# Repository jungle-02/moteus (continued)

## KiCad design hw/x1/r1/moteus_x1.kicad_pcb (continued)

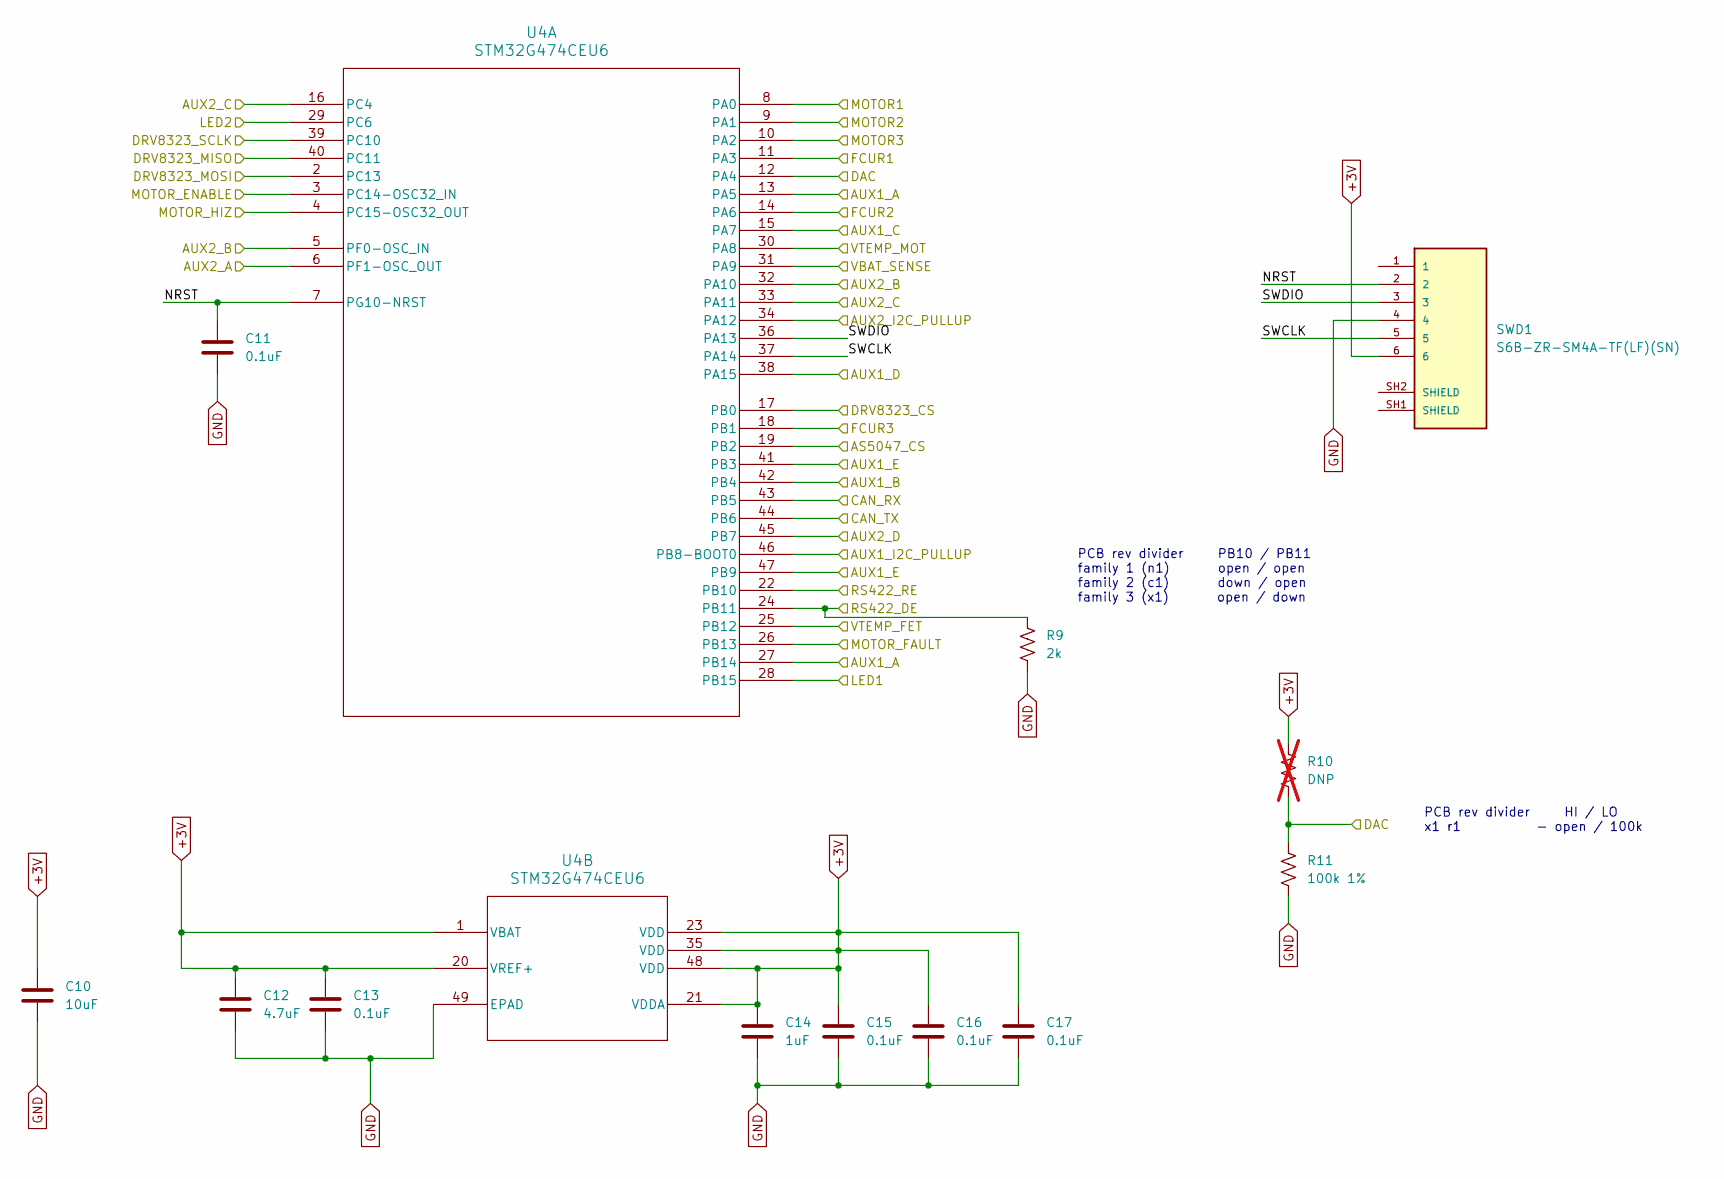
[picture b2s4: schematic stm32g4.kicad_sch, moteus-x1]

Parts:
C10: 10uF; C_1206_3216Metric; MPN MF-CAP-1206-10uF
C11, C13, C15, C16, C17: 0.1uF; C_0402_1005Metric; MPN MF-CAP-0402-0.1uF
C12: 4.7uF; C_0603_1608Metric; MPN CL10A475KP8NNNC
C14: 1uF; C_0402_1005Metric; MPN MF-CAP-0402-1uF
R9: 2k; R_0402_1005Metric; MPN MF-RES-0402-2K
R10: DNP; R_0402_1005Metric; not fitted
R11: 100k 1%; R_0402_1005Metric; MPN RC0402FR-07100KL
SWD1: S6B-ZR-SM4A-TF(LF)(SN); JST_S6B-ZR-SM4A-TF(LF)(SN); MPN S6B-ZR-SM4A-TF(LF)(SN)
U4: STM32G474CEU6; UFQFPN-48_7X7X0P55MM; MPN STM32G474CEU6

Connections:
+3V: C10.1, C12.1, C13.1, C14.1, C15.1, C16.1, C17.1, R10.1, SWD1.6, U4.1 (VBAT), U4.20 (VREF+), U4.21 (VDDA), U4.23 (VDD), U4.35 (VDD), U4.48 (VDD); also elsewhere on the board
/CAN/CAN_RX: U4.43 (PB5); also elsewhere on the board
/CAN/CAN_TX: U4.44 (PB6); also elsewhere on the board
/Current Sense/FCUR1: U4.11 (PA3); also elsewhere on the board
/Current Sense/FCUR2: U4.14 (PA6); also elsewhere on the board
/Current Sense/FCUR3: U4.18 (PB1); also elsewhere on the board
/Gate Driver/DRV8323_CS: U4.17 (PB0); also elsewhere on the board
/Gate Driver/DRV8323_FAULT: U4.26 (PB13); also elsewhere on the board
/Gate Driver/DRV8323_MISO: U4.40 (PC11); also elsewhere on the board
/Gate Driver/DRV8323_MOSI: U4.2 (PC13); also elsewhere on the board
/Gate Driver/DRV8323_SCLK: U4.39 (PC10); also elsewhere on the board
/Gate Driver/MOTOR1: U4.8 (PA0); also elsewhere on the board
/Gate Driver/MOTOR2: U4.9 (PA1); also elsewhere on the board
/Gate Driver/MOTOR3: U4.10 (PA2); also elsewhere on the board
/Gate Driver/MOTOR_ENABLE: U4.3 (PC14-OSC32_IN); also elsewhere on the board
/Gate Driver/MOTOR_HIZ: U4.4 (PC15-OSC32_OUT); also elsewhere on the board
/LED Sense/DAC: R10.2, R11.1, U4.12 (PA4); also elsewhere on the board
/LED Sense/LED1: U4.28 (PB15); also elsewhere on the board
/LED Sense/LED2: U4.29 (PC6); also elsewhere on the board
/VT Sense/VBAT_SENSE: U4.31 (PA9); also elsewhere on the board
/VT Sense/VTEMP_FET: U4.25 (PB12); also elsewhere on the board
/VT Sense/VTEMP_MOT: U4.30 (PA8); also elsewhere on the board
/aux1/AS5047_CS: U4.19 (PB2); also elsewhere on the board
/aux1/AUX1_A: U4.13 (PA5), U4.27 (PB14); also elsewhere on the board
/aux1/AUX1_B: U4.42 (PB4); also elsewhere on the board
/aux1/AUX1_C: U4.15 (PA7); also elsewhere on the board
/aux1/AUX1_D: U4.38 (PA15); also elsewhere on the board
/aux1/AUX1_E: U4.41 (PB3), U4.47 (PB9); also elsewhere on the board
/aux1/AUX1_I2C_PULLUP: U4.46 (PB8-BOOT0); also elsewhere on the board
/aux2/AUX2_A: U4.6 (PF1-OSC_OUT); also elsewhere on the board
/aux2/AUX2_B: U4.5 (PF0-OSC_IN), U4.32 (PA10); also elsewhere on the board
/aux2/AUX2_C: U4.16 (PC4), U4.33 (PA11); also elsewhere on the board
/aux2/AUX2_D: U4.45 (PB7); also elsewhere on the board
/aux2/AUX2_I2C_PULLUP: U4.34 (PA12); also elsewhere on the board
/rs422/RS422_DE: R9.1, U4.24 (PB11); also elsewhere on the board
/rs422/RS422_RE: U4.22 (PB10); also elsewhere on the board
/stm32g4/NRST: C11.1, SWD1.2, U4.7 (PG10-NRST)
/stm32g4/SWCLK: SWD1.5, U4.37 (PA14)
/stm32g4/SWDIO: SWD1.3, U4.36 (PA13)
GND: C10.2, C11.2, C12.2, C13.2, C14.2, C15.2, C16.2, C17.2, R9.2, R11.2, SWD1.4, U4.49 (EPAD); also elsewhere on the board

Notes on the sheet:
PCB rev divider HI / LO x1 r1 - open / 100k
PCB rev divider PB10 / PB11 family 1 (n1) open / open family 2 (c1) down / open family 3 (x1) open / down

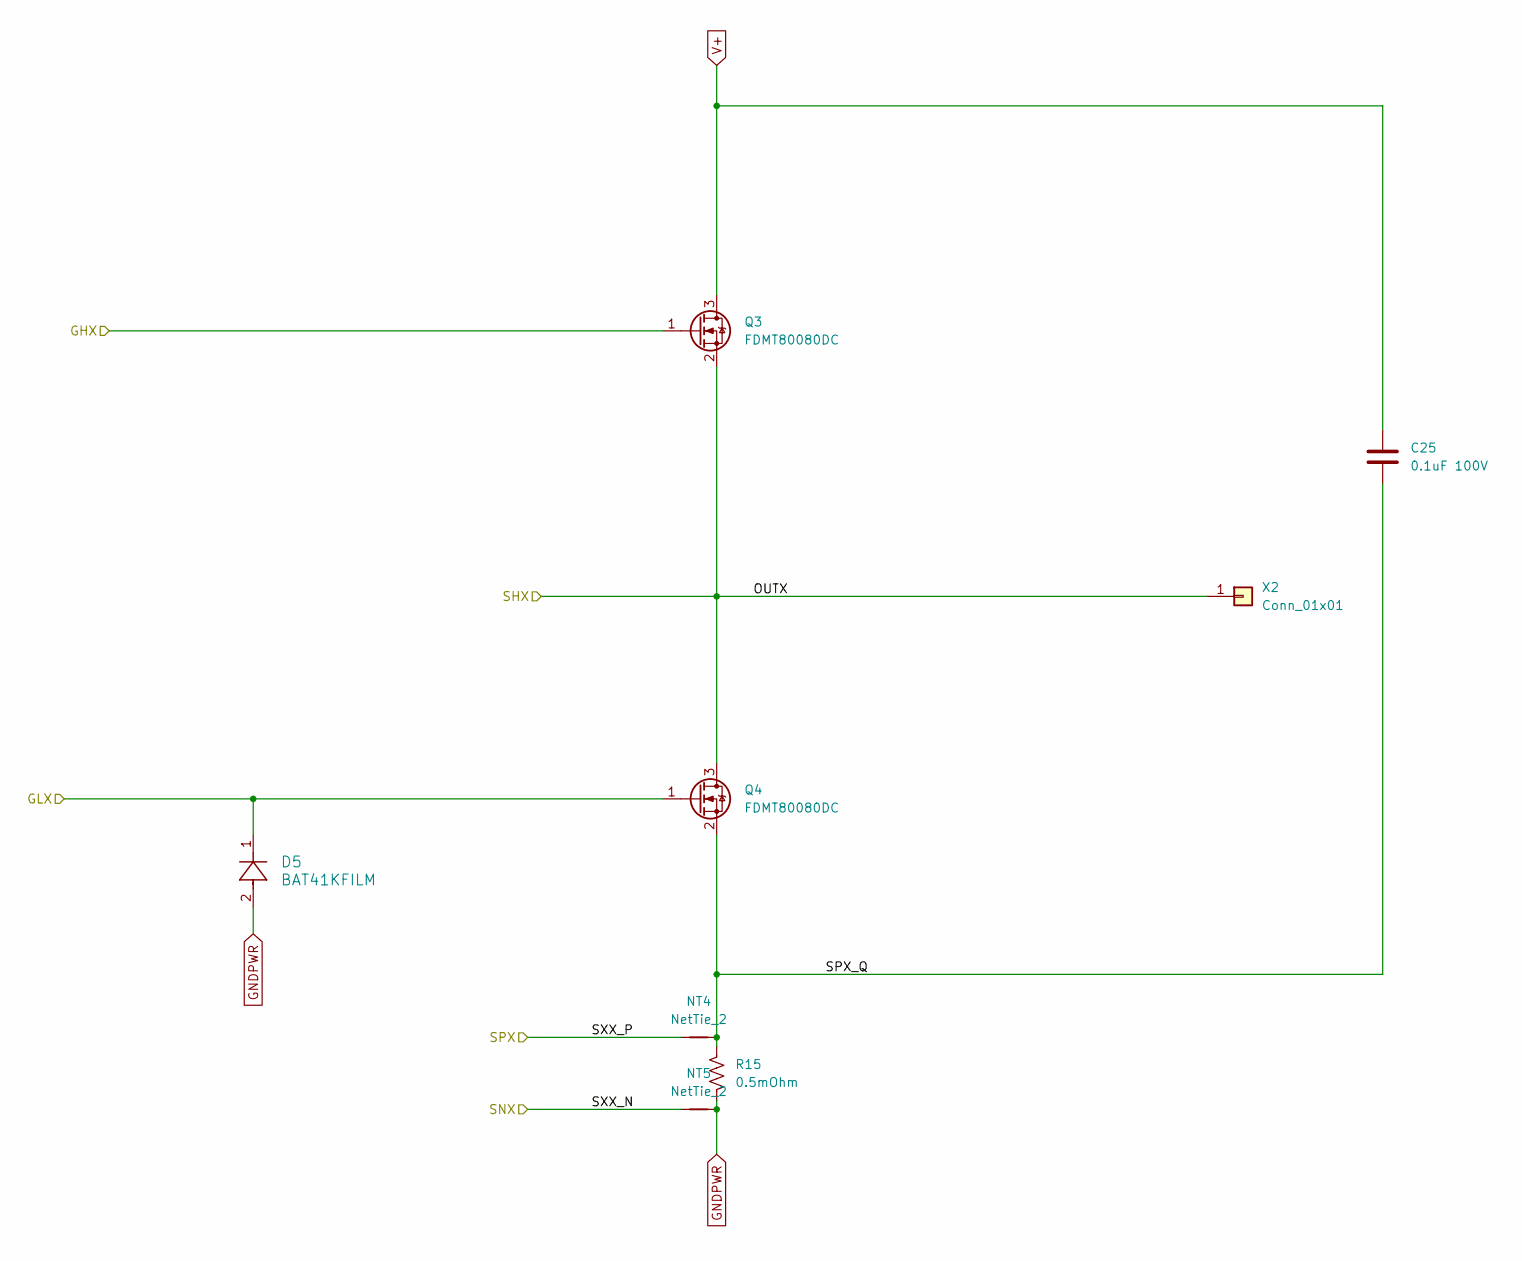
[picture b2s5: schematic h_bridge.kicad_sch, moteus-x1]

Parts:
C25: 0.1uF 100V; C_1812_4532Metric; MPN 18121C104MAT2A
D5: BAT41KFILM; SOD-523_STM; MPN BAT41KFILM
NT4, NT5: NetTie_2; NetTie-2_SMD_Pad0.2
Q3, Q4: FDMT80080DC; PQFN_8x8; MPN FDMT80080DC
R15: 0.5mOhm; R_2512_6332Metric; MPN WSLF2512L5000FEA
X2: Conn_01x01; POWER_M2.5

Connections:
/Gate Driver/GHB: Q3.1 (G); also elsewhere on the board
/Gate Driver/GLB: D5.1, Q4.1 (G); also elsewhere on the board
/H Bridge B/OUTX: Q3.2 (S), Q4.3 (D), X2.1; also elsewhere on the board
/H Bridge B/SPX_Q: C25.2, NT4.2, Q4.2 (S), R15.1
/H Bridge B/SXX_N: NT5.1; also elsewhere on the board
/H Bridge B/SXX_P: NT4.1; also elsewhere on the board
GNDPWR: D5.2, NT5.2, R15.2; also elsewhere on the board
V+: C25.1, Q3.3 (D); also elsewhere on the board

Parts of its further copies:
C24, C26: 0.1uF 100V; C_1812_4532Metric; MPN 18121C104MAT2A
D4, D6: BAT41KFILM; SOD-523_STM; MPN BAT41KFILM
NT2, NT3, NT6, NT7: NetTie_2; NetTie-2_SMD_Pad0.2
Q1, Q2, Q5, Q6: FDMT80080DC; PQFN_8x8; MPN FDMT80080DC
R14, R16: 0.5mOhm; R_2512_6332Metric; MPN WSLF2512L5000FEA
X1, X3: Conn_01x01; POWER_M2.5

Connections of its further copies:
/Gate Driver/GHA: Q1.1 (G); also elsewhere on the board
/Gate Driver/GHC: Q5.1 (G); also elsewhere on the board
/Gate Driver/GLA: D4.1, Q2.1 (G); also elsewhere on the board
/Gate Driver/GLC: D6.1, Q6.1 (G); also elsewhere on the board
/H Bridge A/OUTX: Q1.2 (S), Q2.3 (D), X1.1; also elsewhere on the board
/H Bridge A/SPX_Q: C24.2, NT2.2, Q2.2 (S), R14.1
/H Bridge A/SXX_N: NT3.1; also elsewhere on the board
/H Bridge A/SXX_P: NT2.1; also elsewhere on the board
/H Bridge C/OUTX: Q5.2 (S), Q6.3 (D), X3.1; also elsewhere on the board
/H Bridge C/SPX_Q: C26.2, NT6.2, Q6.2 (S), R16.1
/H Bridge C/SXX_N: NT7.1; also elsewhere on the board
/H Bridge C/SXX_P: NT6.1; also elsewhere on the board
GNDPWR: D4.2, D6.2, NT3.2, NT7.2, R14.2, R16.2; also elsewhere on the board
V+: C24.1, C26.1, Q1.3 (D), Q5.3 (D); also elsewhere on the board

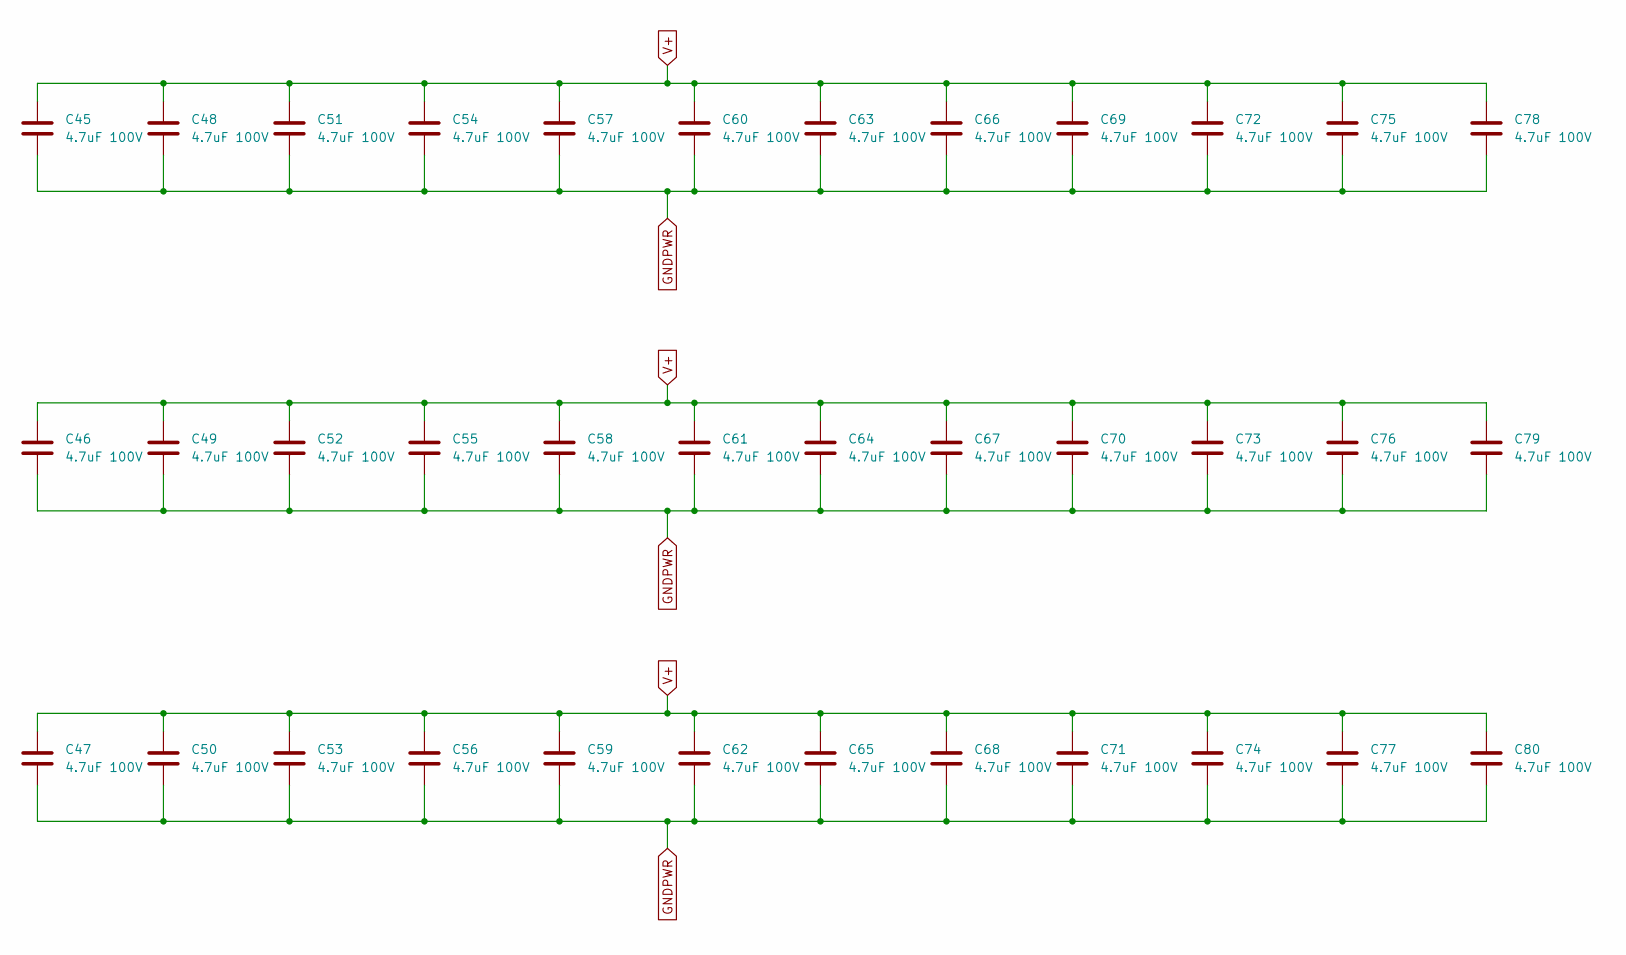
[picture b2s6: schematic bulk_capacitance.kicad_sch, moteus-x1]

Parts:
C45, C46, C47, C48, C49, C50, C51, C52, C53, C54, C55, C56, C57, C58, C59, C60, C61, C62, C63, C64, C65, C66, C67, C68, C69, C70, C71, C72, C73, C74, C75, C76, C77, C78, C79, C80: 4.7uF 100V; C_1206_3216Metric; MPN GRJ31CC72A475KE01K

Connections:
GNDPWR: C45.2, C46.2, C47.2, C48.2, C49.2, C50.2, C51.2, C52.2, C53.2, C54.2, C55.2, C56.2, C57.2, C58.2, C59.2, C60.2, C61.2, C62.2, C63.2, C64.2, C65.2, C66.2, C67.2, C68.2, C69.2, C70.2, C71.2, C72.2, C73.2, C74.2, C75.2, C76.2, C77.2, C78.2, C79.2, C80.2; also elsewhere on the board
V+: C45.1, C46.1, C47.1, C48.1, C49.1, C50.1, C51.1, C52.1, C53.1, C54.1, C55.1, C56.1, C57.1, C58.1, C59.1, C60.1, C61.1, C62.1, C63.1, C64.1, C65.1, C66.1, C67.1, C68.1, C69.1, C70.1, C71.1, C72.1, C73.1, C74.1, C75.1, C76.1, C77.1, C78.1, C79.1, C80.1; also elsewhere on the board

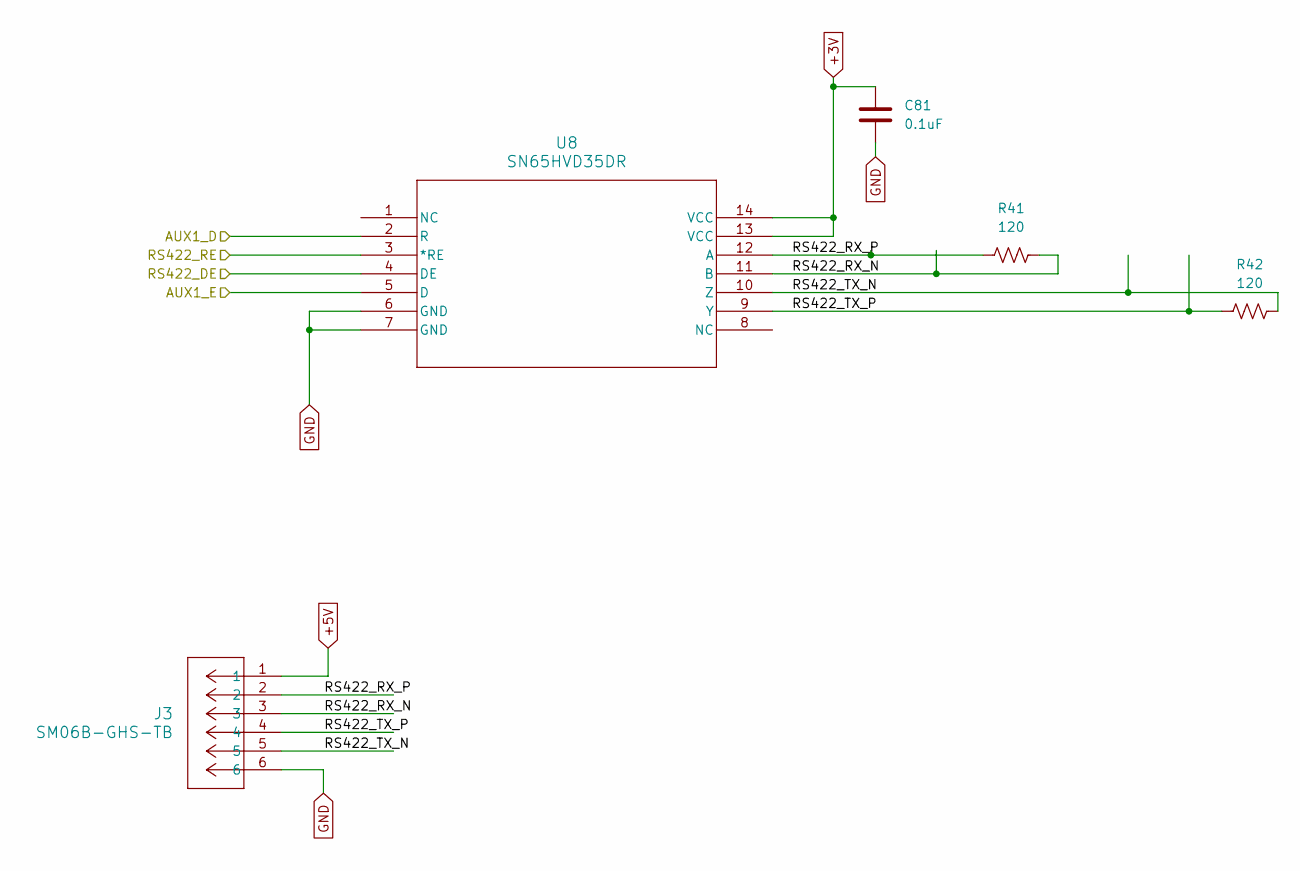
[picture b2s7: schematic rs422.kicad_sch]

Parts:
C81: 0.1uF; C_0402_1005Metric; MPN MF-CAP-0402-0.1uF
J3: SM06B-GHS-TB; CONN_SM06B-GHS-TB_JST; MPN SM06B-GHS-TB(LF)(SN)
R41, R42: 120; R_0402_1005Metric; MPN RC0402FR-07120RL
U8: SN65HVD35DR; D14; MPN SN65HVD35DR

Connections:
+3V: C81.1, U8.13 (VCC), U8.14 (VCC); also elsewhere on the board
+5V: J3.1; also elsewhere on the board
/aux1/AUX1_D: U8.2 (R); also elsewhere on the board
/aux1/AUX1_E: U8.5 (D); also elsewhere on the board
/rs422/RS422_DE: U8.4 (DE); also elsewhere on the board
/rs422/RS422_RE: U8.3 (*RE); also elsewhere on the board
/rs422/RS422_RX_N: J3.3, R41.2, U8.11 (B)
/rs422/RS422_RX_P: J3.2, R41.1, U8.12 (A)
/rs422/RS422_TX_N: J3.5, R42.2, U8.10 (Z)
/rs422/RS422_TX_P: J3.4, R42.1, U8.9 (Y)
GND: C81.2, J3.6, U8.6 (GND), U8.7 (GND); also elsewhere on the board

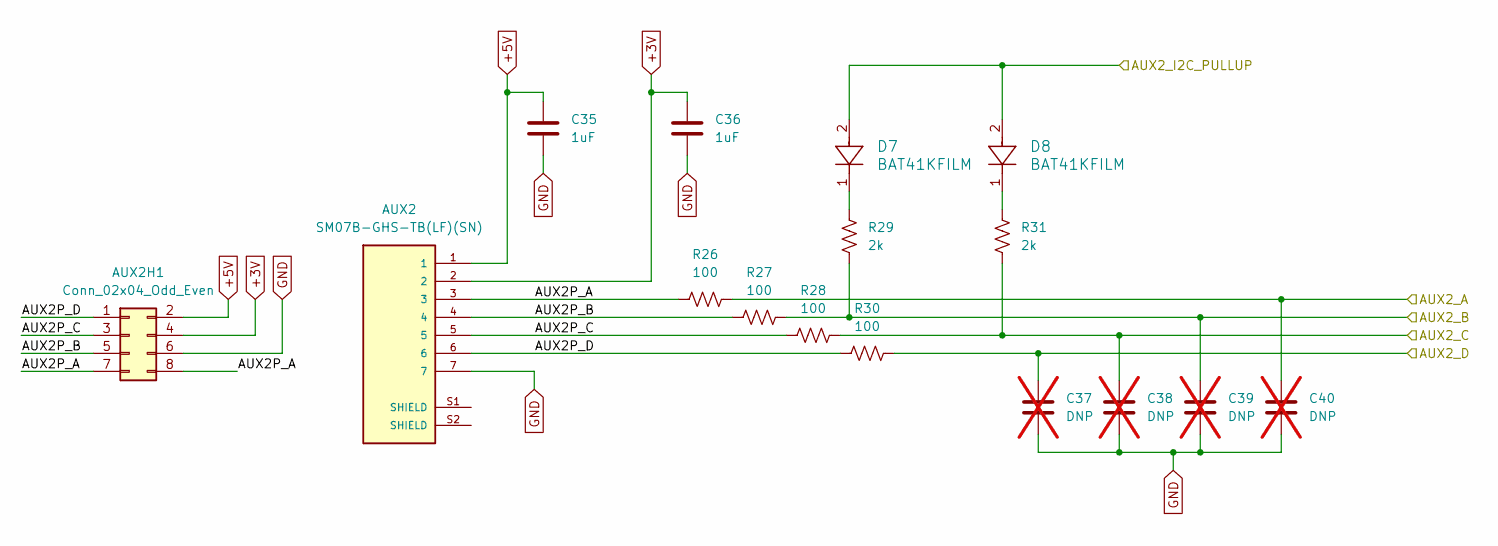
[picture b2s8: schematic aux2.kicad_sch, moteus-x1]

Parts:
AUX2: SM07B-GHS-TB(LF)(SN); JST_SM07B-GHS-TB(LF)(SN); MPN SM07B-GHS-TB(LF)(SN)
AUX2H1: Conn_02x04_Odd_Even; PinHeader_2x04_P1.27mm_Vertical
C35, C36: 1uF; C_0402_1005Metric; MPN MF-CAP-0402-1uF
C37, C38, C39, C40: DNP; C_0402_1005Metric; not fitted
D7, D8: BAT41KFILM; SOD-523_STM; MPN BAT41KFILM
R26, R27, R28, R30: 100; R_0402_1005Metric; MPN MF-RES-0402-100
R29, R31: 2k; R_0402_1005Metric; MPN MF-RES-0402-2K

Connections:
+3V: AUX2.2, AUX2H1.4, C36.1; also elsewhere on the board
+5V: AUX2.1, AUX2H1.2, C35.1; also elsewhere on the board
/aux2/AUX2P_A: AUX2.3, AUX2H1.7, AUX2H1.8, R26.1
/aux2/AUX2P_B: AUX2.4, AUX2H1.5, R27.1
/aux2/AUX2P_C: AUX2.5, AUX2H1.3, R28.1
/aux2/AUX2P_D: AUX2.6, AUX2H1.1, R30.1
/aux2/AUX2_A: C40.1, R26.2; also elsewhere on the board
/aux2/AUX2_B: C39.1, R27.2, R29.2; also elsewhere on the board
/aux2/AUX2_C: C38.1, R28.2, R31.2; also elsewhere on the board
/aux2/AUX2_D: C37.1, R30.2; also elsewhere on the board
/aux2/AUX2_I2C_PULLUP: D7.2, D8.2; also elsewhere on the board
GND: AUX2.7, AUX2H1.6, C35.2, C36.2, C37.2, C38.2, C39.2, C40.2; also elsewhere on the board
unnamed: D7.1, R29.1
unnamed: D8.1, R31.1

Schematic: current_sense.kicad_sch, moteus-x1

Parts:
C27, C28, C29: 1000pF; C_0402_1005Metric; MPN MF-CAP-0402-1nF
R17, R18, R19: 22; R_0402_1005Metric; MPN MF-RES-0402-22

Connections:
/Current Sense/CUR1: R17.1; also elsewhere on the board
/Current Sense/CUR2: R18.1; also elsewhere on the board
/Current Sense/CUR3: R19.1; also elsewhere on the board
/Current Sense/FCUR1: C27.1, R17.2; also elsewhere on the board
/Current Sense/FCUR2: C28.1, R18.2; also elsewhere on the board
/Current Sense/FCUR3: C29.1, R19.2; also elsewhere on the board
GND: C27.2, C28.2, C29.2; also elsewhere on the board

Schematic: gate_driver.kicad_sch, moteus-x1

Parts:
C18: 1uF; C_0603_1608Metric; MPN MF-CAP-0603-1uF
C19: 0.1uF 100V; C_0603_1608Metric; MPN GCJ188R72A104KA01D
C20: 1uF; C_0402_1005Metric; MPN MF-CAP-0402-1uF
C21: 1uF 25V; C_0603_1608Metric; MPN C1608X7R1E105K080AE
C22: 47nF 100V; C_0603_1608Metric; MPN C0603X473K1RAC7867
C23: 1uF; C_0603_1608Metric; MPN C1608X7R1E105K080AE
R12, R13: 2k; R_0402_1005Metric; MPN MF-RES-0402-2K
U5: DRV8353SRTAR; RTA0040B; MPN DRV8353SRTAR

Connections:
+3V: C18.2, R12.1, R13.1, U5.24 (VREF); also elsewhere on the board
+12V: C19.2, U5.3 (VM); also elsewhere on the board
/Current Sense/CUR1: U5.21 (SOC); also elsewhere on the board
/Current Sense/CUR2: U5.22 (SOB); also elsewhere on the board
/Current Sense/CUR3: U5.23 (SOA); also elsewhere on the board
/Gate Driver/CPH: C22.2, U5.2 (CPH)
/Gate Driver/CPL: C22.1, U5.1 (CPL)
/Gate Driver/DRV8323_CS: U5.30 (SCS_N); also elsewhere on the board
/Gate Driver/DRV8323_FAULT: R13.2, U5.26 (FAULT_N); also elsewhere on the board
/Gate Driver/DRV8323_MISO: R12.2, U5.27 (SDO); also elsewhere on the board
/Gate Driver/DRV8323_MOSI: U5.28 (SDI); also elsewhere on the board
/Gate Driver/DRV8323_SCLK: U5.29 (SCLK); also elsewhere on the board
/Gate Driver/GHA: U5.6 (GHA); also elsewhere on the board
/Gate Driver/GHB: U5.15 (GHB); also elsewhere on the board
/Gate Driver/GHC: U5.16 (GHC); also elsewhere on the board
/Gate Driver/GLA: U5.8 (GLA); also elsewhere on the board
/Gate Driver/GLB: U5.13 (GLB); also elsewhere on the board
/Gate Driver/GLC: U5.18 (GLC); also elsewhere on the board
/Gate Driver/MOTOR1: U5.32 (INHA); also elsewhere on the board
/Gate Driver/MOTOR2: U5.34 (INHB); also elsewhere on the board
/Gate Driver/MOTOR3: U5.36 (INHC); also elsewhere on the board
/Gate Driver/MOTOR_ENABLE: U5.31 (ENABLE); also elsewhere on the board
/Gate Driver/MOTOR_HIZ: U5.33 (INLA), U5.35 (INLB), U5.37 (INLC); also elsewhere on the board
/H Bridge A/OUTX: U5.7 (SHA); also elsewhere on the board
/H Bridge A/SXX_N: U5.10 (SNA); also elsewhere on the board
/H Bridge A/SXX_P: U5.9 (SPA); also elsewhere on the board
/H Bridge B/OUTX: U5.14 (SHB); also elsewhere on the board
/H Bridge B/SXX_N: U5.11 (SNB); also elsewhere on the board
/H Bridge B/SXX_P: U5.12 (SPB); also elsewhere on the board
/H Bridge C/OUTX: U5.17 (SHC); also elsewhere on the board
/H Bridge C/SXX_N: U5.20 (SNC); also elsewhere on the board
/H Bridge C/SXX_P: U5.19 (SPC); also elsewhere on the board
GND: C18.1, C20.1, C23.1, U5.25 (AGND); also elsewhere on the board
GNDPWR: C19.1, U5.39 (PGND), U5.41 (PAD); also elsewhere on the board
unnamed: C20.2, U5.38 (DVDD)
unnamed: C21.2, U5.5 (VCP)
unnamed: C23.2, U5.40 (VGLS)
V+: C21.1, U5.4 (VDRAIN); also elsewhere on the board

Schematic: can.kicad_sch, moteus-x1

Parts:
C30, C31: 0.1uF; C_0402_1005Metric; MPN MF-CAP-0402-0.1uF
CAN1, CAN2: S3B-PH-SM4-TB(LF)(SN); JST_S3B-PH-SM4-TB(LF)(SN); MPN S3B-PH-SM4-TB(LF)(SN)
CAN_DBG1: Conn_01x03_Pin; PinHeader_1x03_P2.00mm_Vertical
R20: 120; R_0603_1608Metric; not fitted
U6: TCAN1057AEV-Q1; SOIC-8_3.9x4.9mm_P1.27mm; MPN TCAN1057AEVDRQ1

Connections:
+3V: C30.1, U6.5 (VIO); also elsewhere on the board
+5V: C31.1, U6.3 (VCC); also elsewhere on the board
/CAN/CAN_N: CAN1.2, CAN2.2, CAN_DBG1.2, R20.2, U6.6 (CANL)
/CAN/CAN_P: CAN1.1, CAN2.1, CAN_DBG1.1, R20.1, U6.7 (CANH)
/CAN/CAN_RX: U6.4 (RXD); also elsewhere on the board
/CAN/CAN_TX: U6.1 (TXD); also elsewhere on the board
GND: C30.2, C31.2, CAN1.3, CAN2.3, CAN_DBG1.3, U6.2 (GND), U6.8 (STB), U6.9 (PAD); also elsewhere on the board

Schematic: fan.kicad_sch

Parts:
C82: 4.7uF; C_1206_3216Metric; MPN GRJ31CC72A475KE01K
FAN1: Conn_01x04_Pin; PinSocket_2x02_P2.54mm_Vertical
R43, R44: 100; R_0402_1005Metric; MPN MF-RES-0402-100

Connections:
+12V: C82.1, FAN1.2; also elsewhere on the board
/aux2/AUX2_C: R43.1; also elsewhere on the board
/aux2/AUX2_D: R44.1; also elsewhere on the board
GND: C82.2, FAN1.1; also elsewhere on the board
unnamed: FAN1.3, R44.2
unnamed: FAN1.4, R43.2

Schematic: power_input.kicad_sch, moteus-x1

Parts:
C1: 1uF 100V; C_0805_2012Metric; MPN GCM21BC72A105KE36L
C2: 0.1uF 100V; C_0603_1608Metric; MPN GCJ188R72A104KA01D
C3, C6: 1uF; C_0402_1005Metric; MPN MF-CAP-0402-1uF
C4, C7, C9: 22uF; C_1210_3225Metric; MPN GRM32ER71E226KE15L
C5: 5600pF; C_0402_1005Metric; MPN GCM155R71E562KA37D
C8: DNP; C_0402_1005Metric; not fitted
D3: SMBJ51D-M3/I; D_SMB; MPN SMBJ51D-M3/I
D13: US1B; D_SMA; MPN STPS1H100A
J1: XT30PW-M; AMASS_XT30PW-M; MPN XT30PW-M
J4: Conn_01x02_Pin; PinHeader_1x02_P2.00mm_Vertical
L1, L3: 2.2uH; IND_DFE252012_MUR; MPN DFE252012PD-2R2M=P2
L2: 100uH; IND_6028-WE-LQS_WRE; MPN 74404063101
M1, M2, M3, M4: Conn_01x01_Pin; M3_MOUNT_CORNER
NT1: NetTie_2; NetTie-2_SMD_Pad0.254mm
R1: 42.2k 1%; R_0402_1005Metric; MPN RC0402FR-0742K2L
R2: 69.8k 1%; R_0402_1005Metric; MPN RC0402FR-0769K8L
R3: 80.6k 1%; R_0402_1005Metric; MPN RC0402FR-0780K6L
R4: 22; R_0402_1005Metric; MPN MF-RES-0402-22
R5: 52.3k 1%; R_0402_1005Metric; MPN RC0402FR-0752K3L
R6: 226k 1%; R_0402_1005Metric; MPN RC0402FR-07226KL
R7: 16.2k 1%; R_0402_1005Metric; MPN RC0402FR-0716K2L
R8: DNP; R_0402_1005Metric; not fitted
TP1, TP2, TP3: TestPoint; TestPoint_THTPad_D1.5mm_Drill0.7mm
U1: MAX17760ATC+; 21-0664E_1233-1C_MXM; MPN MAX17760ATC+
U2, U3: TPS629203DRLR; SOT-5x3_DRL0008A_TEX; MPN TPS629203DRLR
VN1: Conn_01x01; POWER_M2.5
VP1: Conn_01x01; POWER_M2.5

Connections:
+3V: C9.1, L3.1, TP3.1, U3.3 (VOS); also elsewhere on the board
+5V: C4.1, D13.1 (K), L1.1, TP1.1, U2.3 (VOS), U3.6 (VIN), U3.7 (EN); also elsewhere on the board
+12V: C7.1, L2.1, R4.2, R6.1, TP2.1, U2.6 (VIN), U2.7 (EN); also elsewhere on the board
/Power Input/5V_IN: D13.2 (A), J4.1
GND: C4.2, C6.2, C7.2, C9.2, J4.2, NT1.2, R1.2, R3.2, R5.2, R7.2, U2.5 (GND), U3.5 (GND); also elsewhere on the board
GNDPWR: C1.2, C2.2, C3.2, C5.2, C8.2, D3.2 (A2), J1.N, NT1.1, R2.2, R8.2, U1.2 (PGND), U1.10 (MODE), U1.11 (SGND), U1.13 (EPAD), VN1.1; also elsewhere on the board
MOUNT_GND: C8.1, M4.1, R8.1
unnamed: C6.1, R4.1, U1.7 (EXTVCC)
unnamed: R6.2, R7.1, U1.8 (FB)
unnamed: L2.2, U1.12 (LX)
unnamed: R2.1, U1.6 (RT/SYNC)
unnamed: C5.1, U1.9 (SS)
unnamed: C3.1, U1.3 (VCC)
unnamed: R3.1, U2.1 (FB/VSET)
unnamed: R1.1, U2.8 (MODE/S-CONF)
unnamed: L1.2, U2.4 (SW)
unnamed: R5.1, U3.8 (MODE/S-CONF)
unnamed: L3.2, U3.4 (SW)
V+: C1.1, C2.1, D3.1 (A1), J1.P, U1.1 (VIN), VP1.1; also elsewhere on the board

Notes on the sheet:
FB: VSET FSW: 2.5MHz Output Discharge: No Mode: Auto PFM
FB: VSET FSW: 2.5MHz Output Discharge: No Mode: FPWM
0.9ms soft start
OPEN = 3.3V
400kHz

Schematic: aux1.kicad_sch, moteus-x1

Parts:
AUX1: SM08B-GHS-TB; CONN_SM08B-GHS-TB_JST; MPN SM08B-GHS-TB(LF)(SN)
AUX1_S1: Conn_01x04; PinHeader_1x04_P1.27mm_Vertical
C41, C42, C43: 1uF; C_0402_1005Metric; MPN MF-CAP-0402-1uF
C44: 0.1uF; C_0402_1005Metric; MPN MF-CAP-0402-0.1uF
D9, D10: BAT41KFILM; SOD-523_STM; MPN BAT41KFILM
R32, R33, R34, R35, R36: 100; R_0402_1005Metric; MPN MF-RES-0402-100
R37, R38: 2k; R_0402_1005Metric; MPN MF-RES-0402-2K
U7: MA600; QFN-16-1EP_3x3mm_P0.5mm_EP1.75x1.75mm; MPN MA600GQE-0000

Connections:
+3V: AUX1.2, AUX1_S1.1, C42.1, C43.1, C44.1, U7.13 (VDD), U7.14 (AVDD); also elsewhere on the board
+5V: AUX1.1, C41.1; also elsewhere on the board
/aux1/AS5047_CS: U7.5 (~CS); also elsewhere on the board
/aux1/AUX1P_A: AUX1.3, R32.1
/aux1/AUX1P_B: AUX1.4, R33.1
/aux1/AUX1P_C: AUX1.5, R34.1
/aux1/AUX1P_D: AUX1.6, AUX1_S1.2, R35.1
/aux1/AUX1P_E: AUX1.7, AUX1_S1.3, R36.1
/aux1/AUX1_A: R32.2, U7.12 (SCLK); also elsewhere on the board
/aux1/AUX1_B: R33.2, U7.7 (MISO); also elsewhere on the board
/aux1/AUX1_C: R34.2, U7.4 (MOSI); also elsewhere on the board
/aux1/AUX1_D: R35.2, R37.2; also elsewhere on the board
/aux1/AUX1_E: R36.2, R38.2; also elsewhere on the board
/aux1/AUX1_I2C_PULLUP: D9.2, D10.2; also elsewhere on the board
GND: AUX1.8, AUX1_S1.4, C41.2, C42.2, C43.2, C44.2, U7.8 (GND), U7.10 (TEST); also elsewhere on the board
unnamed: D9.1, R37.1
unnamed: D10.1, R38.1

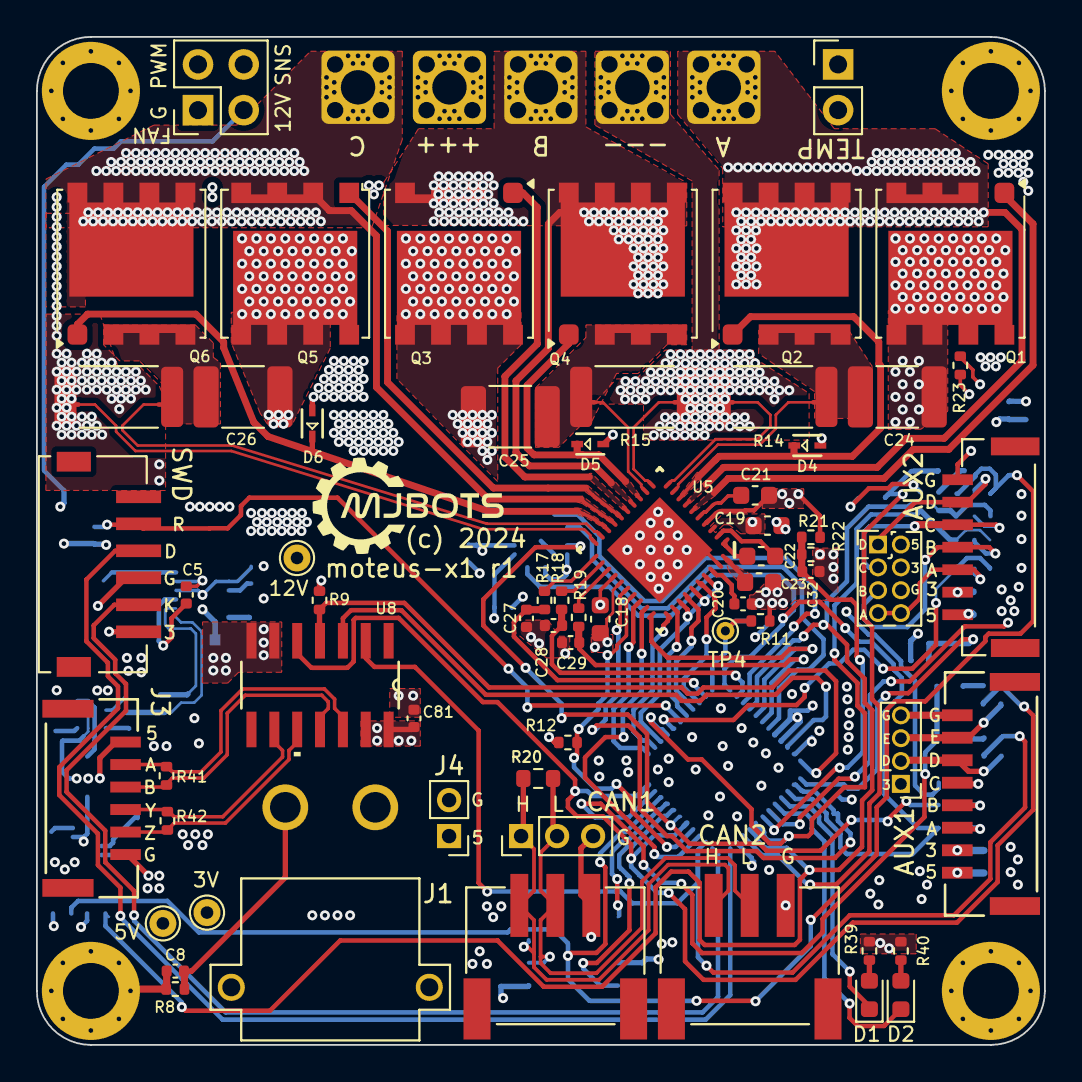
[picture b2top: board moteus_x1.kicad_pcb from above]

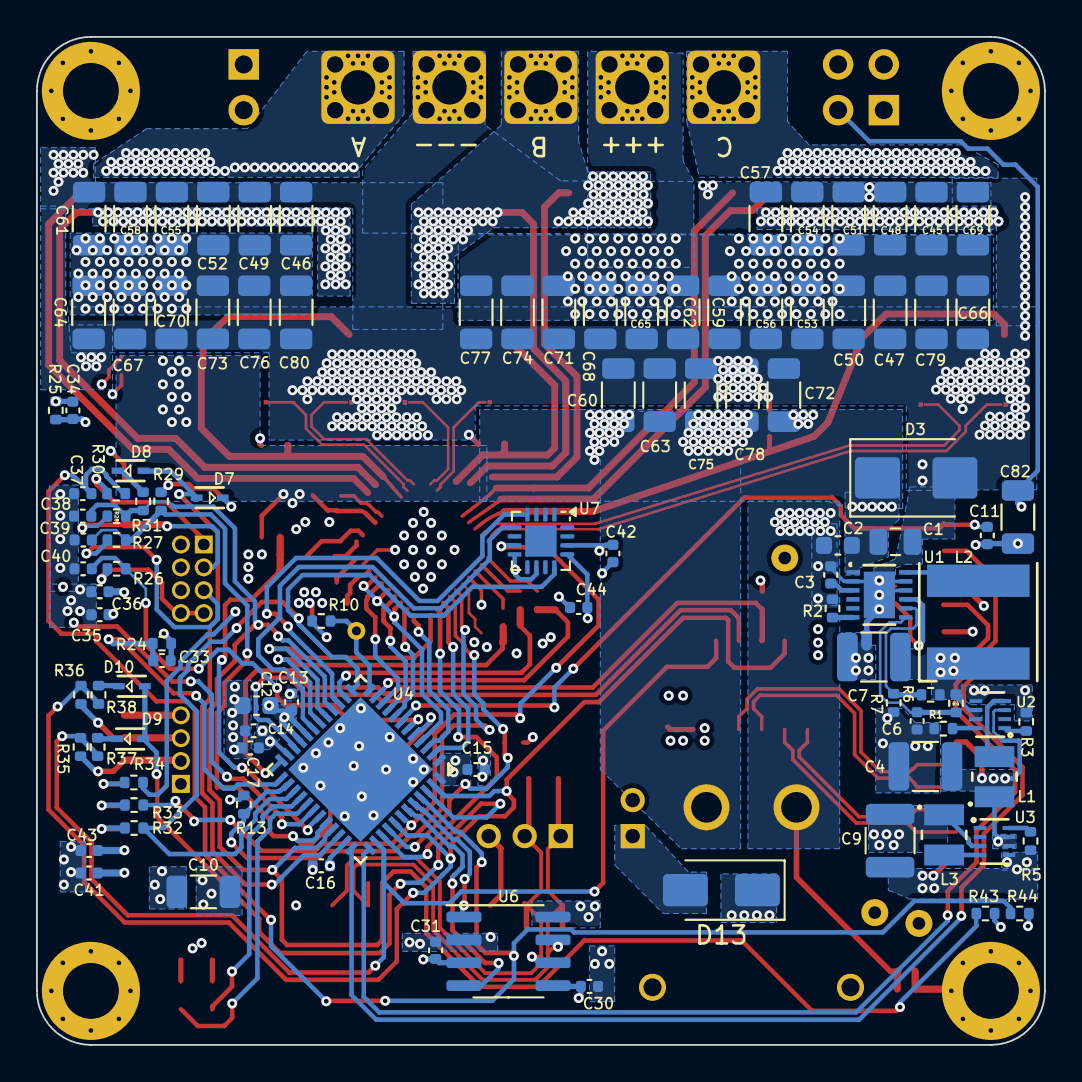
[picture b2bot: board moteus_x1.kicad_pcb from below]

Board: 6 copper layers, 56.0 x 56.0 mm, 187 parts (108 on the bottom side), 106 nets.

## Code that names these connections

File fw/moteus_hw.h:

// Copyright 2023 mjbots Robotic Systems, LLC.  info@mjbots.com
//
// Licensed under the Apache License, Version 2.0 (the "License");
// you may not use this file except in compliance with the License.
// You may obtain a copy of the License at
//
//     http://www.apache.org/licenses/LICENSE-2.0
//
// Unless required by applicable law or agreed to in writing, software
// distributed under the License is distributed on an "AS IS" BASIS,
// WITHOUT WARRANTIES OR CONDITIONS OF ANY KIND, either express or implied.
// See the License for the specific language governing permissions and
// limitations under the License.

#pragma once

#include "mbed.h"

#include "fw/millisecond_timer.h"

namespace moteus {

//////////////////////////////////////////
// The following "families" are supported:
//  moteus    - family 0
//  moteus-n1 - family 1
//  moteus-c1 - family 2
//
// Each family has an independent hardware version timeline, and
// possibly a different mechanism for verifying hardware version
// compatibility.


// This structure is filled in once the family and hardware version
// are known.
struct MoteusHwPins {
  PinName pwm1 = PA_0_ALT0;
  PinName pwm2 = PA_1_ALT0;
  PinName pwm3 = PA_2_ALT0;

  PinName drv8323_enable = NC;
  PinName drv8323_hiz = NC;
  PinName drv8323_cs = NC;

  PinName drv8323_mosi = NC;
  PinName drv8323_miso = NC;
  PinName drv8323_sck = NC;
  PinName drv8323_fault = NC;

  PinName debug_led1 = NC;
  PinName power_led = NC;

  PinName current1 = NC;
  PinName current2 = NC;
  PinName current3 = NC;

  PinName vsense = NC;
  PinName tsense = PA_9;

  PinName msense = NC;

  float vsense_adc_scale = 0.0f;

  PinName uart_tx = NC;
  PinName uart_rx = NC;
  PinName uart_dir = NC;

  PinName as5047_cs = NC;

  PinName can_td = NC;
  PinName can_rd = NC;

  PinName debug1 = NC;
  PinName debug2 = NC;
  PinName debug_dac = PA_4;

  uint32_t model_number = 0;

  uint32_t firmware_version = 0x000105;

  // Each board has a power limit curve, below a bus voltage V_l, the
  // P_l power limit is used.  Above bus voltage V_h, P_h power limit
  // is used.  Between, the power limit is linearly interpolated.  All
  // power limits are normalized to 30kHz PWM.
  float power_P_l_W = 0.0f;
  float power_V_l = 24.0f;
  float power_P_h_W = 0.0f;
  float power_V_h = 34.0f;
};


struct FamilyAndVersion {
  int family = 0;
  int hw_version = 0;
  int hw_pins = 0;
};

// Return what family we are executing on.
FamilyAndVersion DetectMoteusFamily(MillisecondTimer*);

MoteusHwPins FindHardwarePins(FamilyAndVersion);


// The "FIRMWARE_VERSION" is a misnomer.  It instead is the equivalent
// of an ABI version, and is incremented when configuration values
// change in a way that would not result in equivalent behavior across
// an upgrade/downgrade.

// Version history:

// # 0x0101 #
//
// * Fixed the calculation of feedforward voltage to have the correct
//   sign for the velocity component.  Previous firmwares,
//   inappropriately applied a negative feedforward term, which
//   counteracted rotation instead of being an actual feedforward.

// # 0x0102 #
//
// * Removed servo.feedforward_scale entirely

// # 0x0103 #
//
// * Added servo.pwm_scale, and for r4.8 boards changed the default
//   value of pwm_comp_off / pwm_comp_mag.

// # 0x0104 #
//
// * Added configurable PWM rates, which changed default values of
//   pwm_comp_mag and pwm_comp_off.

// # 0x0105 #
//
// * Switched to a new encoder and position subsystem.

// # 0x0106 #
//
// * Switched aux?.sources.x.i2c.poll_ms to poll_rate_us to match UART
//   and give more resolution.

// # 0x0107 #
//
// * Fixed motor_position.output.sign == -1 so that DQ commands for
//   voltage or current are inverted, so that positive Q axis voltage
//   or current results in positive speed

// # 0x0108 #
//
// * The default value of `servo.bemf_feedforward` was changed from
//   1.0 to 0.0.

// # 0x0109 #
//
// * Commutation compensation now interpolates, which means old tables
//   need to be upgraded during the flash process.
// * The motor thermistor value is now configurable and defaults to
//   10k instead of 47k.

// # 0x010a #
//
// * servo.max_power_W now defaults to NaN, and if present is used as
//   an absolute value rather than as a "nominal" value.

// # 0x010b #
//
// * servo.flux_brake_margin_voltage replaces
//   servo.flux_brake_min_voltage
// * servo.temperature_margin replaces servo.derate_temperature
// * servo.motor_temperature_margin replaces
//   servo.motor_derate_temperature

// # 0x010c #
//
// * motor_position.sources.x.pll_filter_hz was previously specified
//   in terms of a somewhat arbitrary "natural frequency", but is now
//   specified in terms of the 3dB cutoff frequency

#define MOTEUS_MODEL_NUMBER 0x0000
#define MOTEUS_FIRMWARE_VERSION 0x00010c

extern MoteusHwPins g_hw_pins;

// Ensure the DRV8323 is turned off.
void MoteusEnsureOff();

}

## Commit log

2025-11-09 Fix another typo in the new docs
2025-11-09 Cau hinh Bazel tao compile_commands
2025-11-10 Ignore Bazel build outputs and external dependencies
2026-04-17 add fw_estimate
2026-04-29 Initial plan
2026-04-29 Add fw/mpc_kalman_estimator.h: MPC + Kalman Filter estimator for BLDC motor control
    Agent-Logs-Url: https://github.com/jungle-02/moteus/sessions/e9e625f3-5912-45d7-819a-79ee3ac8f89e
2026-04-29 Fix review findings: p_f cast, step trajectory angle, Inv22 epsilon guard, Cholesky comment
    Agent-Logs-Url: https://github.com/jungle-02/moteus/sessions/e9e625f3-5912-45d7-819a-79ee3ac8f89e
2026-04-29 Improve Mineq_ comment clarity (upper/lower constraint block labels)
    Agent-Logs-Url: https://github.com/jungle-02/moteus/sessions/e9e625f3-5912-45d7-819a-79ee3ac8f89e
2026-05-05 add fw_smo2
2026-05-05 Add comprehensive system flowchart for MPC+Kalman+SMO+RLS integration
2026-05-28 Document real SVPWM firmware execution sequence
